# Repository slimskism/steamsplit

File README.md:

# SteamSplit
The SteamSplit is a single controller split column staggered keyboard with a num pad in the middle.  It also has RGB underglow suuport.  It uses a raspberry pi pico for the controller.

It is a 3x6 layout with a three button thumb cluster, additionally two more keys are available as an encoder alternative adjacent the index finger position.  The three parts are connected via a 14 pin ribbon cable that due to an oversight in design must be twisted to fit.  A couple of different 3D printable case options are available.  All designs are for the left hand, and can be mirrored in slicer software to get the right hand side. 

Firmware can be found in the firmware file, or you can grab my fork of QMK to set up something else.

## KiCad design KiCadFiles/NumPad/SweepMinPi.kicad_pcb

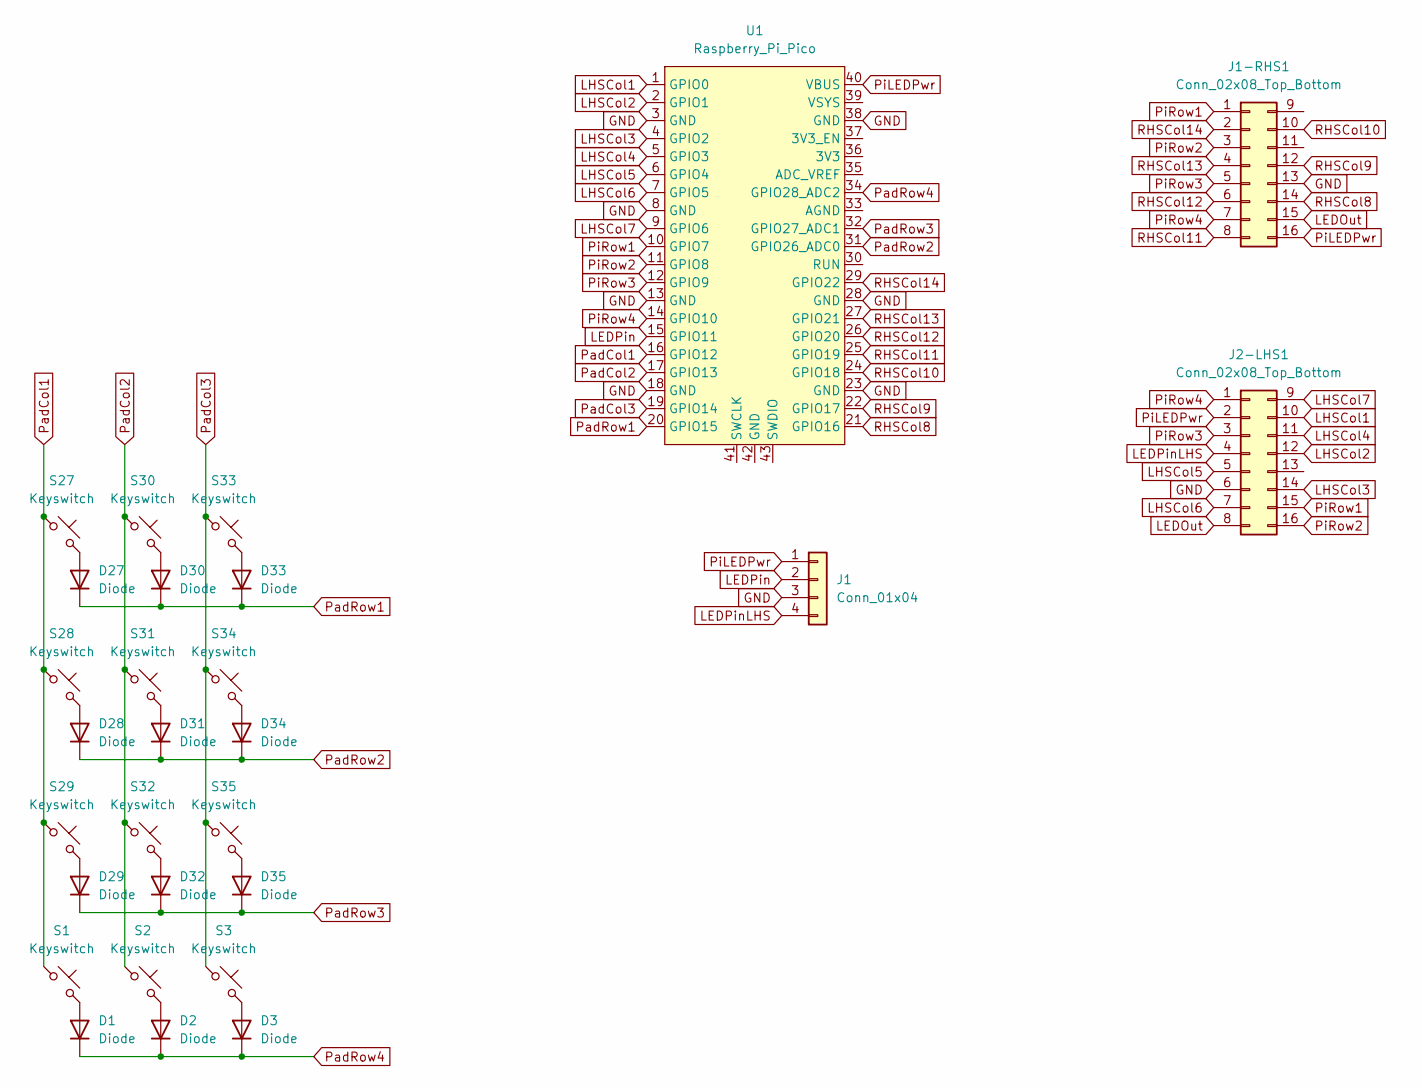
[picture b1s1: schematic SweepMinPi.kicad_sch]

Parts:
D1, D2, D3, D27, D28, D29, D30, D31, D32, D33, D34, D35: Diode; Diode_DO-35
J1: Conn_01x04; PinHeader_1x04_P2.54mm_Vertical
J1-RHS1, J2-LHS1: Conn_02x08_Top_Bottom; IDC-Header_2x08_P2.54mm_Vertical
S1, S2, S3, S27, S28, S29, S30, S31, S32, S33, S34, S35: Keyswitch; Hotswap_MX
U1: Raspberry_Pi_Pico

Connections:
GND: J1.3, J1-RHS1.13, J2-LHS1.6, U1.3 (GND), U1.8 (GND), U1.13 (GND), U1.18 (GND), U1.23 (GND), U1.28 (GND), U1.38 (GND)
LEDOut: J1-RHS1.15, J2-LHS1.8
LEDPin: J1.2, U1.15 (GPIO11)
LEDPinLHS: J1.4, J2-LHS1.4
LHSCol1: J2-LHS1.10, U1.1 (GPIO0)
LHSCol2: J2-LHS1.12, U1.2 (GPIO1)
LHSCol3: J2-LHS1.14, U1.4 (GPIO2)
LHSCol4: J2-LHS1.11, U1.5 (GPIO3)
LHSCol5: J2-LHS1.5, U1.6 (GPIO4)
LHSCol6: J2-LHS1.7, U1.7 (GPIO5)
LHSCol7: J2-LHS1.9, U1.9 (GPIO6)
unnamed: D1.2 (A), S1.2
unnamed: D2.2 (A), S2.2
unnamed: D3.2 (A), S3.2
unnamed: D27.2 (A), S27.2
unnamed: D28.2 (A), S28.2
unnamed: D29.2 (A), S29.2
unnamed: D30.2 (A), S30.2
unnamed: D31.2 (A), S31.2
unnamed: D32.2 (A), S32.2
unnamed: D33.2 (A), S33.2
unnamed: D34.2 (A), S34.2
unnamed: D35.2 (A), S35.2
PadCol1: S1.1, S27.1, S28.1, S29.1, U1.16 (GPIO12)
PadCol2: S2.1, S30.1, S31.1, S32.1, U1.17 (GPIO13)
PadCol3: S3.1, S33.1, S34.1, S35.1, U1.19 (GPIO14)
PadRow1: D27.1 (K), D30.1 (K), D33.1 (K), U1.20 (GPIO15)
PadRow2: D28.1 (K), D31.1 (K), D34.1 (K), U1.31 (GPIO26_ADC0)
PadRow3: D29.1 (K), D32.1 (K), D35.1 (K), U1.32 (GPIO27_ADC1)
PadRow4: D1.1 (K), D2.1 (K), D3.1 (K), U1.34 (GPIO28_ADC2)
PiLEDPwr: J1.1, J1-RHS1.16, J2-LHS1.2, U1.40 (VBUS)
PiRow1: J1-RHS1.1, J2-LHS1.15, U1.10 (GPIO7)
PiRow2: J1-RHS1.3, J2-LHS1.16, U1.11 (GPIO8)
PiRow3: J1-RHS1.5, J2-LHS1.3, U1.12 (GPIO9)
PiRow4: J1-RHS1.7, J2-LHS1.1, U1.14 (GPIO10)
RHSCol8: J1-RHS1.14, U1.21 (GPIO16)
RHSCol9: J1-RHS1.12, U1.22 (GPIO17)
RHSCol10: J1-RHS1.10, U1.24 (GPIO18)
RHSCol11: J1-RHS1.8, U1.25 (GPIO19)
RHSCol12: J1-RHS1.6, U1.26 (GPIO20)
RHSCol13: J1-RHS1.4, U1.27 (GPIO21)
RHSCol14: J1-RHS1.2, U1.29 (GPIO22)

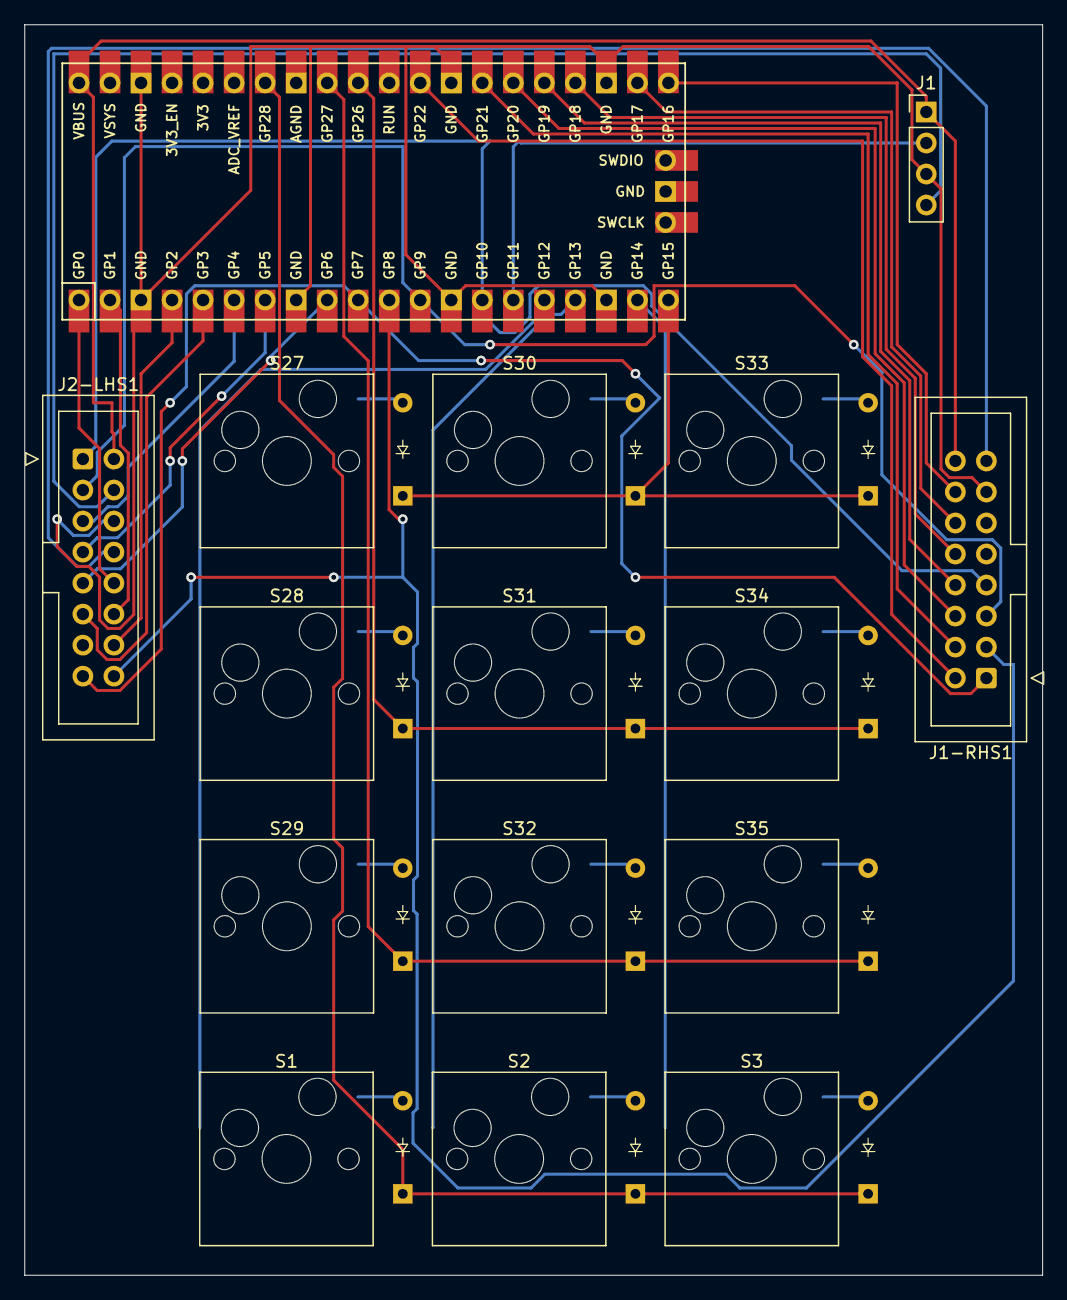
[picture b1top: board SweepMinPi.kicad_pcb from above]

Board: 2 copper layers, 83.3 x 102.4 mm, 28 parts (0 on the bottom side), 42 nets.

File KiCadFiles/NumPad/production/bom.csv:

Designator,Footprint,Quantity,Value,LCSC Part #
"D1, D2, D27, D28, D29, D3, D30, D31, D32, D33, D34, D35",Diode_DO-35,12,Diode,
J1,PinHeader_1x04_P2.54mm_Vertical,1,Conn_01x04,
"J1-RHS1, J2-LHS1",IDC-Header_2x08_P2.54mm_Vertical,2,Conn_02x08_Top_Bottom,
"S1, S2, S27, S28, S29, S3, S30, S31, S32, S33, S34, S35",Hotswap_MX,12,Keyswitch,
U1,Raspberry_Pi_Pico,1,Raspberry_Pi_Pico,

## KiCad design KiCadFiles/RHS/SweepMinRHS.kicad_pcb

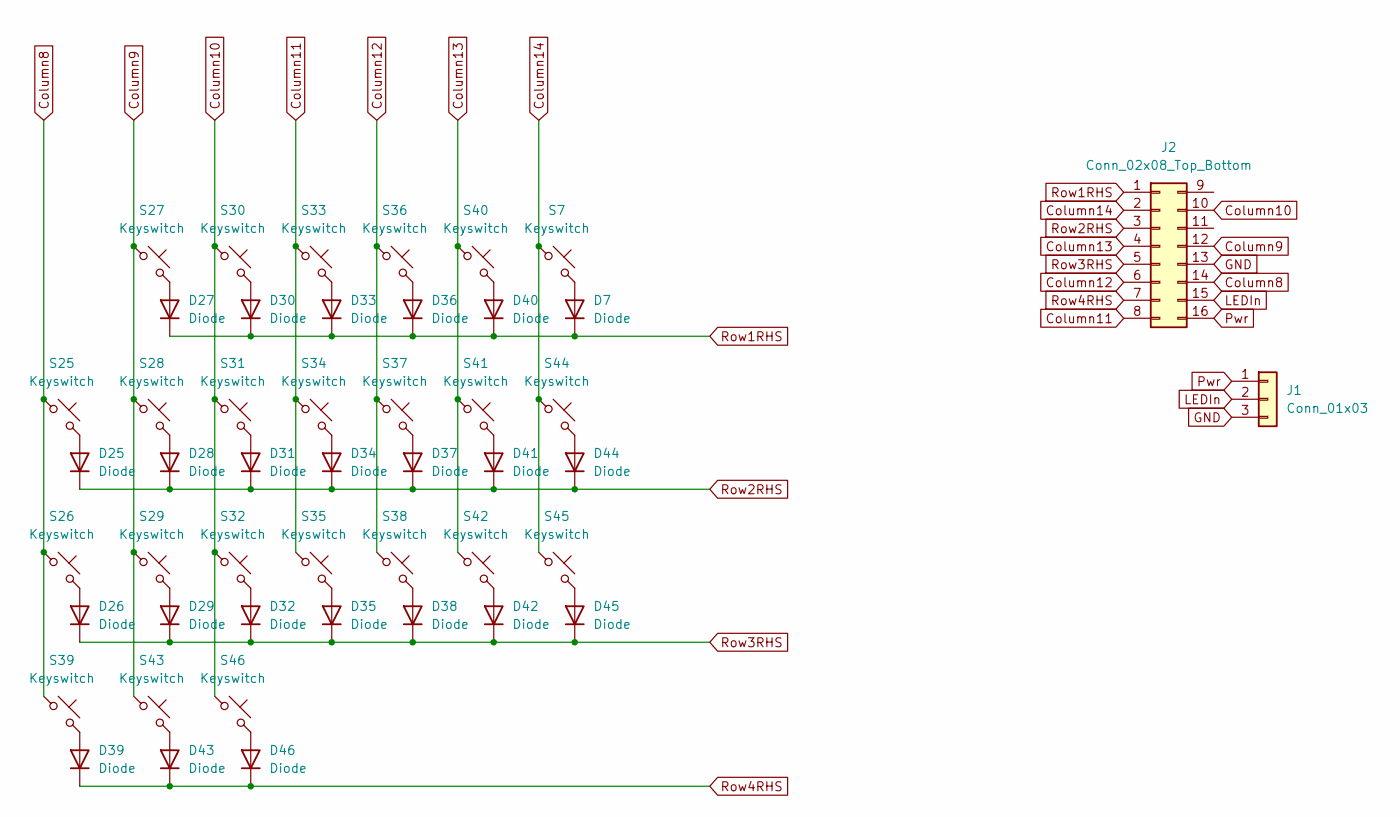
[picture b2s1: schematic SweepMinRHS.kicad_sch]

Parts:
D7, D25, D26, D27, D28, D29, D30, D31, D32, D33, D34, D35, D36, D37, D38, D39, D40, D41, D42, D43, D44, D45, D46: Diode; Diode_DO-35
J1: Conn_01x03; PinHeader_1x03_P2.54mm_Vertical
J2: Conn_02x08_Top_Bottom; IDC-Header_2x08_P2.54mm_Vertical
S7, S25, S26, S27, S28, S29, S30, S31, S32, S33, S34, S35, S36, S37, S38, S39, S40, S41, S42, S43, S44, S45, S46: Keyswitch; Hotswap_MX

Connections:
Column8: J2.14, S25.1, S26.1, S39.1
Column9: J2.12, S27.1, S28.1, S29.1, S43.1
Column10: J2.10, S30.1, S31.1, S32.1, S46.1
Column11: J2.8, S33.1, S34.1, S35.1
Column12: J2.6, S36.1, S37.1, S38.1
Column13: J2.4, S40.1, S41.1, S42.1
Column14: J2.2, S7.1, S44.1, S45.1
GND: J1.3, J2.13
LEDIn: J1.2, J2.15
unnamed: D7.2 (A), S7.2
unnamed: D25.2 (A), S25.2
unnamed: D26.2 (A), S26.2
unnamed: D27.2 (A), S27.2
unnamed: D28.2 (A), S28.2
unnamed: D29.2 (A), S29.2
unnamed: D30.2 (A), S30.2
unnamed: D31.2 (A), S31.2
unnamed: D32.2 (A), S32.2
unnamed: D33.2 (A), S33.2
unnamed: D34.2 (A), S34.2
unnamed: D35.2 (A), S35.2
unnamed: D36.2 (A), S36.2
unnamed: D37.2 (A), S37.2
unnamed: D38.2 (A), S38.2
unnamed: D39.2 (A), S39.2
unnamed: D40.2 (A), S40.2
unnamed: D41.2 (A), S41.2
unnamed: D42.2 (A), S42.2
unnamed: D43.2 (A), S43.2
unnamed: D44.2 (A), S44.2
unnamed: D45.2 (A), S45.2
unnamed: D46.2 (A), S46.2
Pwr: J1.1, J2.16
Row1RHS: D7.1 (K), D27.1 (K), D30.1 (K), D33.1 (K), D36.1 (K), D40.1 (K), J2.1
Row2RHS: D25.1 (K), D28.1 (K), D31.1 (K), D34.1 (K), D37.1 (K), D41.1 (K), D44.1 (K), J2.3
Row3RHS: D26.1 (K), D29.1 (K), D32.1 (K), D35.1 (K), D38.1 (K), D42.1 (K), D45.1 (K), J2.5
Row4RHS: D39.1 (K), D43.1 (K), D46.1 (K), J2.7

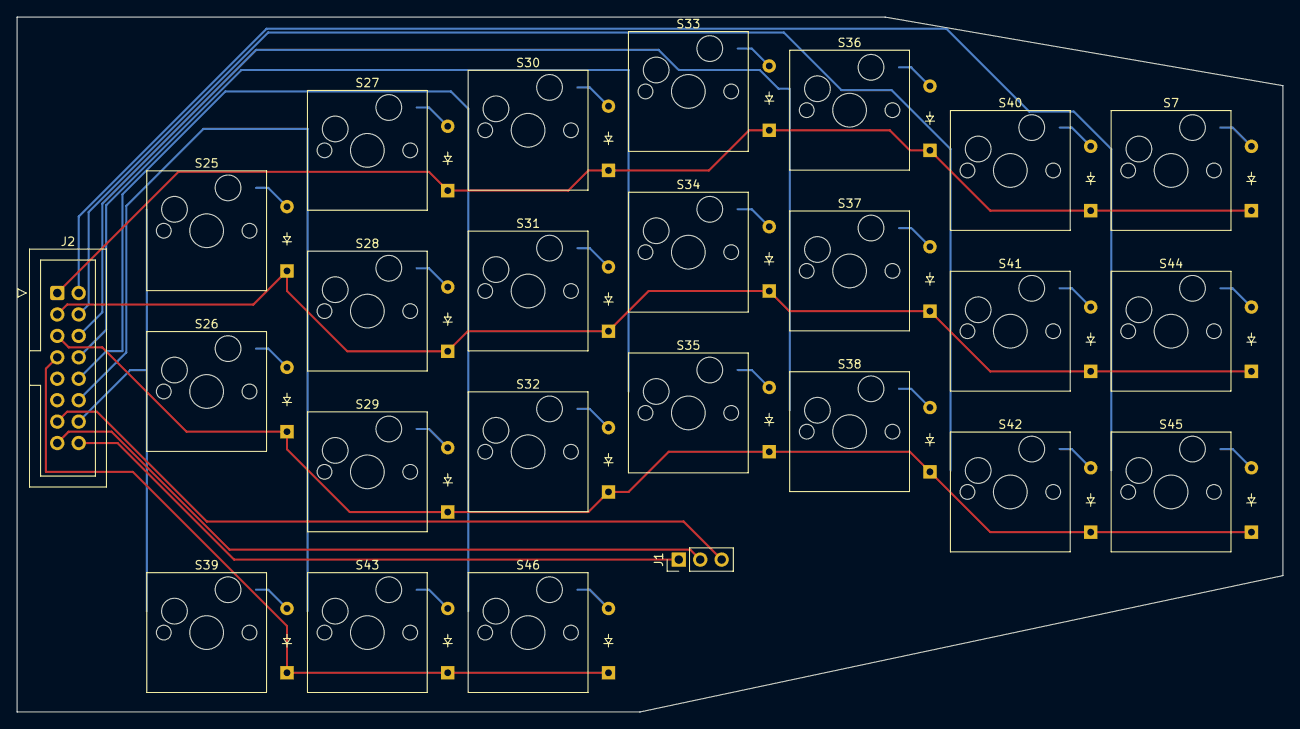
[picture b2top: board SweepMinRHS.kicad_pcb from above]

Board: 2 copper layers, 150.0 x 82.4 mm, 48 parts (0 on the bottom side), 37 nets.

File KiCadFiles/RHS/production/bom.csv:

Designator,Footprint,Quantity,Value,LCSC Part #
"D25, D26, D27, D28, D29, D30, D31, D32, D33, D34, D35, D36, D37, D38, D39, D40, D41, D42, D43, D44, D45, D46, D7",Diode_DO-35,23,Diode,
J1,PinHeader_1x03_P2.54mm_Vertical,1,Conn_01x03,
J2,IDC-Header_2x08_P2.54mm_Vertical,1,Conn_02x08_Top_Bottom,
"S25, S26, S27, S28, S29, S30, S31, S32, S33, S34, S35, S36, S37, S38, S39, S40, S41, S42, S43, S44, S45, S46, S7",Hotswap_MX,23,Keyswitch,
